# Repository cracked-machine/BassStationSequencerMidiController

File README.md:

## BassStationMidiController

### Discussion and Design

- [Part1 – The Synth](https://www.bitshiftmyrobot.com/2021/05/26/novation-bass-station-sequencer-part1/)
- [Part2 – Output](https://www.bitshiftmyrobot.com/2021/06/08/novation-bass-station-sequencer-part2/)
- [Part3 - Input](https://www.bitshiftmyrobot.com/2021/06/08/novation-bass-station-sequencer-part3/)
- [Part4 - Power Supply](https://www.bitshiftmyrobot.com/2021/06/10/novation-bass-station-sequencer-part4/)
- [Part5 - User Interface](https://www.bitshiftmyrobot.com/2021/06/11/novation-bass-station-sequencer-part5-user-interface/)
- [Part6 - Final Design](https://www.bitshiftmyrobot.com/2021/06/13/novation-bass-station-sequencer-part6-bringing-it-all-together/)

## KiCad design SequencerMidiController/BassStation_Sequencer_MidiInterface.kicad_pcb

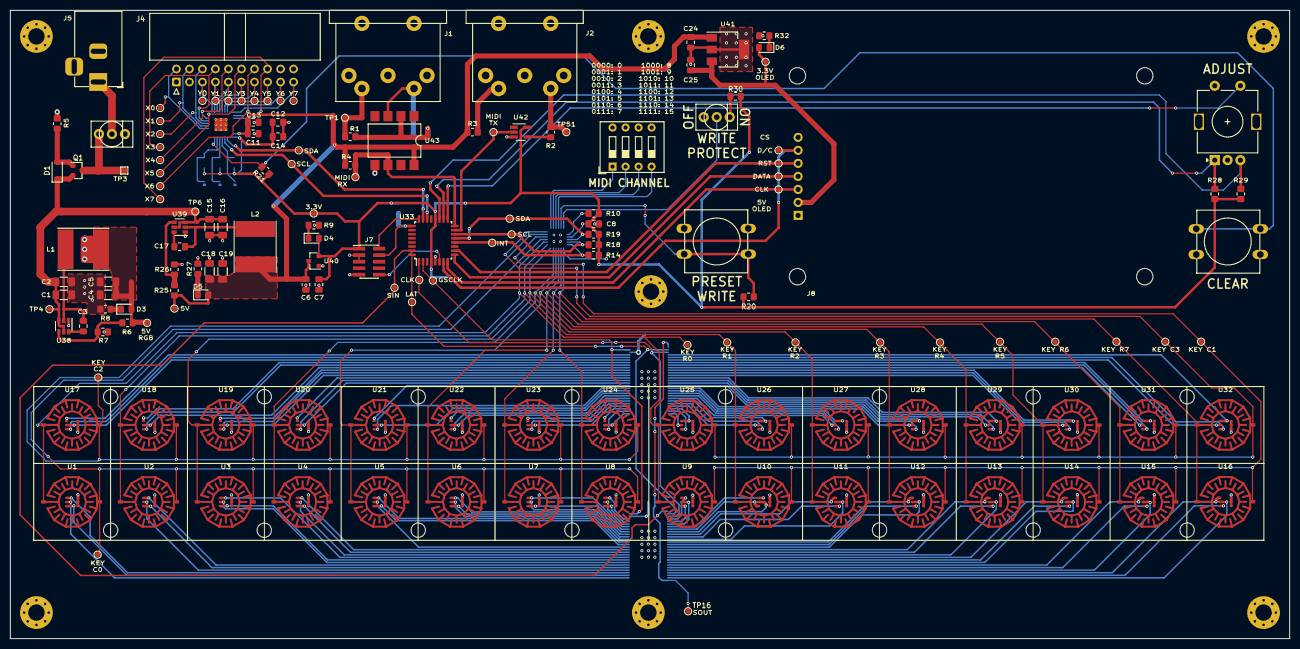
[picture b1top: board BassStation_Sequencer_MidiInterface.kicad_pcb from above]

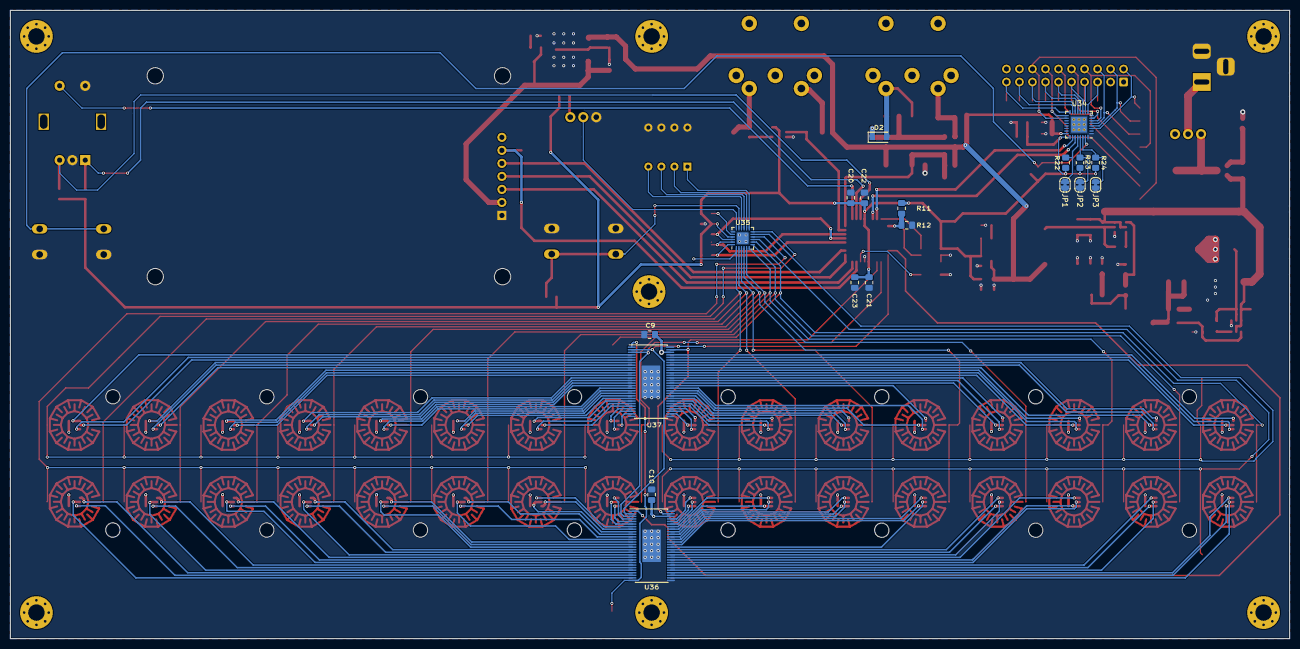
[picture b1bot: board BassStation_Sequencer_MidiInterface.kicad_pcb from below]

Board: 4 copper layers, 249.6 x 122.6 mm, 172 parts (19 on the bottom side), 183 nets.

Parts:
C1, C2, C15, C16: 10uF 20V X5R; R_1206_3216Metric_Pad1.30x1.75mm_HandSolder
C3, C8, C9, C10, C11, C12, C17, C20, C21: 100nF; C_0805_2012Metric_Pad1.18x1.45mm_HandSolder
C4, C5, C18, C19: 22uF 10V X5R; R_1206_3216Metric_Pad1.30x1.75mm_HandSolder
C6, C24, C25: 1uF; C_0805_2012Metric_Pad1.18x1.45mm_HandSolder
C7, C13, C14: 10uF; C_0805_2012Metric_Pad1.18x1.45mm_HandSolder
C22, C23: 4.7uF; C_0805_2012Metric_Pad1.18x1.45mm_HandSolder
CLK: TestPoint; TestPoint_Pad_D1.0mm
D1: MMSZ4694T1G; D_SOD-123
D2: 1N4148; D_SOD-123F
D3, D4, D5, D6: RED; LED_0805_2012Metric_Pad1.15x1.40mm_HandSolder
DATA: TestPoint; TestPoint_Pad_D1.0mm
J1: MIDI IN; RS_5P180_DIN5_SOCKET_WSHIELD
J2: MIDI OUT; RS_5P180_DIN5_SOCKET_WSHIELD
J4: Conn_02x10_Odd_Even; IDC-Header_2x10_P2.54mm_Horizontal
J5: Barrel_Jack_Switch; BarrelJack_Horizontal
J7: Conn_02x05_Odd_Even; PinHeader_2x05_P1.27mm_Vertical_SMD
J8: Conn_01x07; 2.42Inch_OLED_SSD1309
JP1, JP2, JP3: Jumper_NC_Small; SolderJumper-2_P1.3mm_Bridged_RoundedPad1.0x1.5mm
L1, L2: 4.7uH; L_Taiyo-Yuden_NR-80xx_HandSoldering
Q1: Si2323DS; SOT-23
R1, R2, R3, R20, R30: 220R; R_0805_2012Metric_Pad1.20x1.40mm_HandSolder
R4, R10, R14, R18, R19: 4K7; R_0805_2012Metric_Pad1.20x1.40mm_HandSolder
R5: 100R; R_0805_2012Metric_Pad1.20x1.40mm_HandSolder
R6, R25: 56K; R_0805_2012Metric_Pad1.20x1.40mm_HandSolder
R7, R21, R22, R23, R24, R26, R28, R29: 10K; R_0805_2012Metric_Pad1.20x1.40mm_HandSolder
R8, R9, R27, R32: 2K2; R_0805_2012Metric_Pad1.20x1.40mm_HandSolder
R11, R12: 220R; C_0805_2012Metric_Pad1.18x1.45mm_HandSolder
SW1: Rotary_Encoder_Switch; RotaryEncoder_Alps_EC11E-Switch_Vertical_H20mm
SW2: SW_SPDT-2MS1T1B1M2QES; Dailywell_SPDT
SW3: SW_SPST; Dailywell_SPDT
SW4: SW_DIP_x04; SW_DIP_SPSTx04_Slide_9.78x12.34mm_W7.62mm_P2.54mm
SW5, SW7: SW_SPST; SW_PUSH-12mm
TP1, TP2, TP4, TP5, TP6, TP7, TP8, TP9, TP10, TP11, TP13, TP15, TP16, TP17, TP18, TP19, TP20, TP21, TP22, TP23, TP24, TP25, TP26, TP27, TP28, TP29, TP30, TP31, TP32, TP33, TP34, TP35, TP36, TP37, TP38, TP39, TP40, TP41, TP42, TP43, TP44, TP45, TP46, TP47, TP48, TP50, TP51, TP52, TP53: TestPoint; TestPoint_Pad_D1.0mm
TP3: TestPoint; TestPoint_Pad_1.0x1.0mm
U1, U2, U3, U4, U5, U6, U7, U8, U9, U10, U11, U12, U13, U14, U15, U16, U17, U18, U19, U20, U21, U22, U23, U24, U25, U26, U27, U28, U29, U30, U31, U32: PCB-SPST_RGB-LED-Counter-Clockwise; Circular_3mm_10mm_Cree_PLLC6_CLY6D-FKC-CK1N1D1BB7D3D3
U33: STM32G0B1_KxTxN_LQFP32; LQFP-32_7x7mm_P0.8mm
U34: ADG2188; QFN-32-1EP_5x5mm_P0.5mm_EP3.1x3.1mm_ThermalVias
U35: ADP5587-ACPZ_LFCSP24; LFCSP-24-1EP_4x4mm_P0.5mm_EP2.3x2.3mm
U36, U37: TLC5955DCA_HTSSOP56; HTSSOP-56-1EP_6.1x14mm_P0.5mm_EP3.61x6.35mm
U38, U39: TPS563200; SOT-23-6
U40: SE8233X2; SOT-23
U41: MCP1703A-3302_SOT223; SOT-223-3_TabPin2
U42: 74LVC1G34; SOT-23-5_HandSoldering
U43: 6N135S; SMDIP-8_W9.53mm
Y0: TestPoint; TestPoint_Pad_D1.0mm

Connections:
+3V3: C7.1, C8.1, C12.1, C14.1, C20.1, C21.1, C22.1, C23.1, D4.2, J7.1, R10.2, R11.1, R14.1, R18.2, R19.1, R20.2, R21.1, R22.1, R23.1, R24.1, R28.1, R29.1, R30.2, TP8.1, U33.4, U33.20, U34.25, U35.21, U40.2, U42.5
+5V: C6.1, C11.1, C13.1, C18.1, C19.1, C24.1, D5.2, L2.2, R3.2, R4.2, R25.1, TP7.1, U34.24, U40.3, U41.1, U43.8
/CrossPoint Output Switching/A0: JP1.1, R22.2, U34.28
/CrossPoint Output Switching/A1: JP2.1, R23.2, U34.29
/CrossPoint Output Switching/A2: JP3.1, R24.2, U34.30
/CrossPoint Output Switching/ADG2188_SCL: TP42.1, U33.22, U34.27
/CrossPoint Output Switching/ADG2188_SDA: TP40.1, U33.23, U34.26
/CrossPoint Output Switching/X0: J4.2, TP39.1, U34.3
/CrossPoint Output Switching/X1: J4.4, TP38.1, U34.4
/CrossPoint Output Switching/X2: J4.6, TP37.1, U34.5
/CrossPoint Output Switching/X3: J4.8, TP36.1, U34.6
/CrossPoint Output Switching/X4: J4.10, TP35.1, U34.7
/CrossPoint Output Switching/X5: J4.12, TP34.1, U34.8
/CrossPoint Output Switching/X6: J4.14, TP33.1, U34.17
/CrossPoint Output Switching/X7: J4.16, TP32.1, U34.18
/CrossPoint Output Switching/Y0: J4.5, U34.9, Y0.1
/CrossPoint Output Switching/Y1: J4.7, TP48.1, U34.10
/CrossPoint Output Switching/Y2: J4.9, TP47.1, U34.11
/CrossPoint Output Switching/Y3: J4.11, TP46.1, U34.12
/CrossPoint Output Switching/Y4: J4.13, TP45.1, U34.13
/CrossPoint Output Switching/Y5: J4.15, TP44.1, U34.14
/CrossPoint Output Switching/Y6: J4.17, TP43.1, U34.15
/CrossPoint Output Switching/Y7: J4.19, TP41.1, U34.16
/Input Keyscan and RGB LED Driver/ADP5587_INT: R14.2, TP23.1, U33.12, U35.24
/Input Keyscan and RGB LED Driver/ADP5587_RST: R10.1, U35.20
/Input Keyscan and RGB LED Driver/ADP5587_SCL: R18.1, TP22.1, U33.14, U35.23
/Input Keyscan and RGB LED Driver/ADP5587_SDA: R19.2, TP21.1, U33.13, U35.22
/Input Keyscan and RGB LED Driver/ADP5587_WRITE: R20.1, SW5.2, U35.17
/Input Keyscan and RGB LED Driver/ADP5587_WRITEPROTECT: SW2.2, U35.18
/Input Keyscan and RGB LED Driver/DIPSW1: SW4.1, U35.13
/Input Keyscan and RGB LED Driver/DIPSW2: SW4.2, U35.14
/Input Keyscan and RGB LED Driver/DIPSW3: SW4.3, U35.15
/Input Keyscan and RGB LED Driver/DIPSW4: SW4.4, U35.16
/Input Keyscan and RGB LED Driver/KEY_C0: TP17.1, U1.8, U2.8, U3.8, U4.8, U5.8, U6.8, U7.8, U8.8, U35.9
/Input Keyscan and RGB LED Driver/KEY_C1: TP18.1, U9.8, U10.8, U11.8, U12.8, U13.8, U14.8, U15.8, U16.8, U35.10
/Input Keyscan and RGB LED Driver/KEY_C2: TP19.1, U17.8, U18.8, U19.8, U20.8, U21.8, U22.8, U23.8, U24.8, U35.11
/Input Keyscan and RGB LED Driver/KEY_C3: TP20.1, U25.8, U26.8, U27.8, U28.8, U29.8, U30.8, U31.8, U32.8, U35.12
/Input Keyscan and RGB LED Driver/KEY_R0: TP24.1, U1.7, U9.7, U17.7, U25.7, U35.8
/Input Keyscan and RGB LED Driver/KEY_R1: TP25.1, U2.7, U10.7, U18.7, U26.7, U35.7
/Input Keyscan and RGB LED Driver/KEY_R2: TP26.1, U3.7, U11.7, U19.7, U27.7, U35.6
/Input Keyscan and RGB LED Driver/KEY_R3: TP27.1, U4.7, U12.7, U20.7, U28.7, U35.5
/Input Keyscan and RGB LED Driver/KEY_R4: TP28.1, U5.7, U13.7, U21.7, U29.7, U35.4
/Input Keyscan and RGB LED Driver/KEY_R5: TP29.1, U6.7, U14.7, U22.7, U30.7, U35.3
/Input Keyscan and RGB LED Driver/KEY_R6: TP30.1, U7.7, U15.7, U23.7, U31.7, U35.2
/Input Keyscan and RGB LED Driver/KEY_R7: TP31.1, U8.7, U16.7, U24.7, U32.7, U35.1
/Input Keyscan and RGB LED Driver/LEDBK1: U1.1, U36.32
/Input Keyscan and RGB LED Driver/LEDBK2: U2.1, U36.35
/Input Keyscan and RGB LED Driver/LEDBK3: U3.1, U36.38
/Input Keyscan and RGB LED Driver/LEDBK4: U4.1, U36.41
/Input Keyscan and RGB LED Driver/LEDBK5: U5.1, U36.44
/Input Keyscan and RGB LED Driver/LEDBK6: U6.1, U36.47
/Input Keyscan and RGB LED Driver/LEDBK7: U7.1, U36.50
/Input Keyscan and RGB LED Driver/LEDBK8: U8.1, U36.53
/Input Keyscan and RGB LED Driver/LEDBK9: U9.1, U36.4
/Input Keyscan and RGB LED Driver/LEDBK10: U10.1, U36.7
/Input Keyscan and RGB LED Driver/LEDBK11: U11.1, U36.10
/Input Keyscan and RGB LED Driver/LEDBK12: U12.1, U36.13
/Input Keyscan and RGB LED Driver/LEDBK13: U13.1, U36.16
/Input Keyscan and RGB LED Driver/LEDBK14: U14.1, U36.19
/Input Keyscan and RGB LED Driver/LEDBK15: U15.1, U36.22
/Input Keyscan and RGB LED Driver/LEDBK16: U16.1, U36.25
/Input Keyscan and RGB LED Driver/LEDBK17: U17.1, U37.53
/Input Keyscan and RGB LED Driver/LEDBK18: U18.1, U37.50
/Input Keyscan and RGB LED Driver/LEDBK19: U19.1, U37.47
/Input Keyscan and RGB LED Driver/LEDBK20: U20.1, U37.44
/Input Keyscan and RGB LED Driver/LEDBK21: U21.1, U37.41
/Input Keyscan and RGB LED Driver/LEDBK22: U22.1, U37.38
/Input Keyscan and RGB LED Driver/LEDBK23: U23.1, U37.35
/Input Keyscan and RGB LED Driver/LEDBK24: U24.1, U37.32
/Input Keyscan and RGB LED Driver/LEDBK25: U25.1, U37.25
/Input Keyscan and RGB LED Driver/LEDBK26: U26.1, U37.22
/Input Keyscan and RGB LED Driver/LEDBK27: U27.1, U37.19
/Input Keyscan and RGB LED Driver/LEDBK28: U28.1, U37.16
/Input Keyscan and RGB LED Driver/LEDBK29: U29.1, U37.13
/Input Keyscan and RGB LED Driver/LEDBK30: U30.1, U37.10
/Input Keyscan and RGB LED Driver/LEDBK31: U31.1, U37.7
/Input Keyscan and RGB LED Driver/LEDBK32: U32.1, U37.4
/Input Keyscan and RGB LED Driver/LEDGK1: U1.2, U36.30
/Input Keyscan and RGB LED Driver/LEDGK2: U2.2, U36.33
/Input Keyscan and RGB LED Driver/LEDGK3: U3.2, U36.36
/Input Keyscan and RGB LED Driver/LEDGK4: U4.2, U36.39
/Input Keyscan and RGB LED Driver/LEDGK5: U5.2, U36.42
/Input Keyscan and RGB LED Driver/LEDGK6: U6.2, U36.45
/Input Keyscan and RGB LED Driver/LEDGK7: U7.2, U36.48
/Input Keyscan and RGB LED Driver/LEDGK8: U8.2, U36.51
/Input Keyscan and RGB LED Driver/LEDGK9: U9.2, U36.6
/Input Keyscan and RGB LED Driver/LEDGK10: U10.2, U36.9
/Input Keyscan and RGB LED Driver/LEDGK11: U11.2, U36.12
/Input Keyscan and RGB LED Driver/LEDGK12: U12.2, U36.15
/Input Keyscan and RGB LED Driver/LEDGK13: U13.2, U36.18
/Input Keyscan and RGB LED Driver/LEDGK14: U14.2, U36.21
/Input Keyscan and RGB LED Driver/LEDGK15: U15.2, U36.24
/Input Keyscan and RGB LED Driver/LEDGK16: U16.2, U36.27
/Input Keyscan and RGB LED Driver/LEDGK17: U17.2, U37.51
/Input Keyscan and RGB LED Driver/LEDGK18: U18.2, U37.48
/Input Keyscan and RGB LED Driver/LEDGK19: U19.2, U37.45
/Input Keyscan and RGB LED Driver/LEDGK20: U20.2, U37.42
/Input Keyscan and RGB LED Driver/LEDGK21: U21.2, U37.39
/Input Keyscan and RGB LED Driver/LEDGK22: U22.2, U37.36
/Input Keyscan and RGB LED Driver/LEDGK23: U23.2, U37.33
/Input Keyscan and RGB LED Driver/LEDGK24: U24.2, U37.30
/Input Keyscan and RGB LED Driver/LEDGK25: U25.2, U37.27
/Input Keyscan and RGB LED Driver/LEDGK26: U26.2, U37.24
/Input Keyscan and RGB LED Driver/LEDGK27: U27.2, U37.21
/Input Keyscan and RGB LED Driver/LEDGK28: U28.2, U37.18
/Input Keyscan and RGB LED Driver/LEDGK29: U29.2, U37.15
/Input Keyscan and RGB LED Driver/LEDGK30: U30.2, U37.12
/Input Keyscan and RGB LED Driver/LEDGK31: U31.2, U37.9
/Input Keyscan and RGB LED Driver/LEDGK32: U32.2, U37.6
/Input Keyscan and RGB LED Driver/LEDRK1: U1.3, U36.31
/Input Keyscan and RGB LED Driver/LEDRK2: U2.3, U36.34
/Input Keyscan and RGB LED Driver/LEDRK3: U3.3, U36.37
/Input Keyscan and RGB LED Driver/LEDRK4: U4.3, U36.40
/Input Keyscan and RGB LED Driver/LEDRK5: U5.3, U36.43
/Input Keyscan and RGB LED Driver/LEDRK6: U6.3, U36.46
/Input Keyscan and RGB LED Driver/LEDRK7: U7.3, U36.49
/Input Keyscan and RGB LED Driver/LEDRK8: U8.3, U36.52
/Input Keyscan and RGB LED Driver/LEDRK9: U9.3, U36.5
/Input Keyscan and RGB LED Driver/LEDRK10: U10.3, U36.8
/Input Keyscan and RGB LED Driver/LEDRK11: U11.3, U36.11
/Input Keyscan and RGB LED Driver/LEDRK12: U12.3, U36.14
/Input Keyscan and RGB LED Driver/LEDRK13: U13.3, U36.17
/Input Keyscan and RGB LED Driver/LEDRK14: U14.3, U36.20
/Input Keyscan and RGB LED Driver/LEDRK15: U15.3, U36.23
/Input Keyscan and RGB LED Driver/LEDRK16: U16.3, U36.26
/Input Keyscan and RGB LED Driver/LEDRK17: U17.3, U37.52
/Input Keyscan and RGB LED Driver/LEDRK18: U18.3, U37.49
/Input Keyscan and RGB LED Driver/LEDRK19: U19.3, U37.46
/Input Keyscan and RGB LED Driver/LEDRK20: U20.3, U37.43
/Input Keyscan and RGB LED Driver/LEDRK21: U21.3, U37.40
/Input Keyscan and RGB LED Driver/LEDRK22: U22.3, U37.37
/Input Keyscan and RGB LED Driver/LEDRK23: U23.3, U37.34
/Input Keyscan and RGB LED Driver/LEDRK24: U24.3, U37.31
/Input Keyscan and RGB LED Driver/LEDRK25: U25.3, U37.26
/Input Keyscan and RGB LED Driver/LEDRK26: U26.3, U37.23
/Input Keyscan and RGB LED Driver/LEDRK27: U27.3, U37.20
/Input Keyscan and RGB LED Driver/LEDRK28: U28.3, U37.17
/Input Keyscan and RGB LED Driver/LEDRK29: U29.3, U37.14
/Input Keyscan and RGB LED Driver/LEDRK30: U30.3, U37.11
/Input Keyscan and RGB LED Driver/LEDRK31: U31.3, U37.8
/Input Keyscan and RGB LED Driver/LEDRK32: U32.3, U37.5
/MCU/MIDI_RX: R4.1, TP2.1, U33.16, U43.6
/MCU/MIDI_TX: TP50.1, U33.15, U42.2
/MCU/NRST: J7.10, U33.6
/MCU/SPI2_CLK: TP10.1, U33.32, U36.2, U37.2
/MCU/SPI2_GSCLK: TP11.1, U33.2, U36.55, U37.55
/MCU/SPI2_LAT: TP15.1, U33.1, U36.3, U37.3
/MCU/SPI2_MOSI: TP13.1, U33.31, U36.1
/MCU/SWDCLK: J7.4, R11.2, R12.1, U33.25
/MCU/SWDIO: J7.2, U33.24
/MCU/TIM1_CH1: R28.2, SW1.A, U33.18
/MCU/TIM1_CH2: R29.2, SW1.B, U33.19
/MCU/TIM1_SW: SW1.S1, U33.17
/OLED_Display/+3.3V_OLED: C25.1, D6.2, J8.2, TP9.1, U41.3
/OLED_Display/CLK: CLK.1, J8.3, U33.8
/OLED_Display/DATA: DATA.1, J8.4, U33.9
/OLED_Display/DATA_COMMAND: J8.6, TP52.1, U33.7
/OLED_Display/RESET: J8.5, TP53.1, U33.10
/PSU/+5V_RGB: C4.1, C5.1, C9.1, C10.1, D3.2, L1.2, R6.1, TP5.1, U1.4, U1.5, U1.6, U2.4, U2.5, U2.6, U3.4, U3.5, U3.6, U4.4, U4.5, U4.6, U5.4, U5.5, U5.6, U6.4, U6.5, U6.6, U7.4, U7.5, U7.6, U8.4, U8.5, U8.6, U9.4, U9.5, U9.6, U10.4, U10.5, U10.6, U11.4, U11.5, U11.6, U12.4, U12.5, U12.6, U13.4, U13.5, U13.6, U14.4, U14.5, U14.6, U15.4, U15.5, U15.6, U16.4, U16.5, U16.6, U17.4, U17.5, U17.6, U18.4, U18.5, U18.6, U19.4, U19.5, U19.6, U20.4, U20.5, U20.6, U21.4, U21.5, U21.6, U22.4, U22.5, U22.6, U23.4, U23.5, U23.6, U24.4, U24.5, U24.6, U25.4, U25.5, U25.6, U26.4, U26.5, U26.6, U27.4, U27.5, U27.6, U28.4, U28.5, U28.6, U29.4, U29.5, U29.6, U30.4, U30.5, U30.6, U31.4, U31.5, U31.6, U32.4, U32.5, U32.6, U36.54, U37.54
/PSU/PMOSReversePolarityProtection/VIN: Q1.3, SW3.1, TP3.1
/PSU/TPS563200_BUCK_MISC/BUCK_VIN: C1.1, C2.1, C15.1, C16.1, D1.1, Q1.2, TP4.1, TP6.1, U38.3, U38.5, U39.3, U39.5
GND: C1.2, C2.2, C4.2, C5.2, C6.2, C7.2, C8.2, C9.2, C10.2, C11.2, C12.2, C13.2, C14.2, C15.2, C16.2, C18.2, C19.2, C20.2, C21.2, C22.2, C23.2, C24.2, C25.2, J5.2, J5.3, J7.3, J7.5, J7.9, J8.1, JP1.2, JP2.2, JP3.2, R5.1, R7.2, R8.2, R9.2, R12.2, R26.2, R27.2, R32.2, SW1.C, SW1.S2, SW2.1, SW4.5, SW4.6, SW4.7, SW4.8, SW5.1, SW7.1, U33.5, U34.1, U34.32, U34.33, U35.19, U35.25, U36.29, U36.56, U36.57, U37.29, U37.56, U37.57, U38.1, U39.1, U40.1, U41.2, U42.3, U43.5
unnamed: C3.1, U38.6
unnamed: C3.2, L1.1, U38.2
unnamed: C17.1, U39.6
unnamed: C17.2, L2.1, U39.2
unnamed: D1.2, Q1.1, R5.2
unnamed: D2.1, R1.1, U43.2
unnamed: D2.2, J1.5, U43.3
unnamed: D3.1, R8.1
unnamed: D4.1, R9.1
unnamed: D5.1, R27.1
unnamed: D6.1, R32.1
unnamed: J1.4, R1.2, TP1.1
unnamed: J2.4, R3.1
unnamed: J2.5, R2.2, TP51.1
unnamed: J5.1, SW3.2
unnamed: R2.1, U42.4
unnamed: R6.2, R7.1, U38.4
unnamed: R21.2, SW7.2, U34.31
unnamed: R25.2, R26.1, U39.4
unnamed: R30.1, SW2.3
unnamed: TP16.1, U36.28, U37.1

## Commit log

2021-06-05 Completed RevA schematics
2021-06-07 RevA Layout draft completed
    - Needs tidy up
    - Add test points
2021-06-07 Added mounting holes to corners of layout
2021-06-07 Completed RevA layout
2021-11-14 updated readme
    started errata section
2022-01-27 Added Keypad spacer STL models
    These plastic spacers will fit around the membrane keypad to keep downward pressure on the leypad when the front panel is in place.
    Photos showing the PCB assembly with and without.
    FYI no front panel has been design yet.
2022-02-08 updated for kicad 6
2022-02-08 updated SPI labels
    https://github.com/cracked-machine/BassStationSequencerMidiController/issues/3
2022-02-09 updated user buttons
    removed dipsw, added four more tactile button (three above display, three below display, six total)
2022-02-09 updated docs
2022-02-09 updated 3d render
2022-02-10 Add ground points
    https://github.com/cracked-machine/BassStationSequencerMidiController/issues/9
    Also, made space on layout for uSDCard IDC connector and DAC analog output section
2022-02-11 updated layout DRC
    Fixed clearance errors with polygons and pads in switch footprints
2022-04-15 Checked microSD card connector pins and added board layout connector footprint
2022-04-15 updated save
2022-06-20 RevB
2022-06-24 Replaced Vias 0.4mm -> 0.45mm
